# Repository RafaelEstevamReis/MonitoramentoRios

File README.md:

# MonitoramentoRios

Repositório do Projeto de Monitoramento de Rios

Acesse o sistema que monitora Rolante no Rio Grande do Sul: [Acessar](https://rios.bitcoineaqui.com.br/)

## Objetivo

Este repositório tem por objetivo desenvolver uma stack de Software e Hardware para monitoramento atmosférico, pluvial e fluvial, com o objetivo de publicar de forma aberta dados precisos a todos que precisarem.

## Arquitetura

O é Sistema altamente integrável, permitindo tanto o uso do Hardware desenvolvido aqui quanto integração de fontes externas, além de ser distribuído replicado em locais geograficamente afastados para redundância e proteção. 

Focando em baixo custo a Placa-mãe foi desenvolida pelo projeto para utilização de sensores amplamente disponíveis

### Detalhes do Hardware

Hardware baseado em ESP32 utilizando PCB customizada para o ambiente úmido da beira de rios mas compatível com DevKits como NodeMCU

Firmware baseado na Stack ESP-Home pela melhor curva de aprendizado de novos colaboradores

### Detalhes do Software

Backend redundante e integrado, recebe dados diretamente de estações, de servidor MQTT externo, de outros Backends, e integrações de sistemas externos

Frontend em Html/JS puro para leveza a simplicidade de treinamento e manutenção

## Agradecimentos Especiais

* A todas as doações em Bitcoin para o projeto [Bitcoin é Aqui](https://bitcoineaqui.com.br) que financiaram a pesquisa e desenvolvimento do projeto
* Ao [Geoge Silva](https://github.com/nitroxgas) por lançar a ideia e desenvolver o primeiro protótipo

## Posso usar o software ou hardware que este repositório desenvolve?

SIM!, mas com ressalvas.

O objetivo deste projeto é compartilhar informações, porém há muitas entidades que coletam os dados e os fecham, tornando-os inúteis para um amplo acesso.
Portanto, se você compartilha seus dados, você pode usar os nossos; se você restringe seus dados, você não pode usar os nossos.

Leia mais abaixo o texto completo do licenciamento antes de contribuir ou utilizar este repositório.

## Como replicar na minha cidade?

Você pode tanto replicar o sistema aqui desenvolvido por conta como integrar ao sistema já mantido pelo Projeto

Para integrar sua cidade no sistema já existente entre em contato com o [Bitcoin é Aqui](https://bitcoineaqui.com.br) ou com a [ACISA de Rolante](https://acisarolante.com/)

## Licença

Este repositório está licenciado sob uma dupla licença (`MIT` e `Licença Restrita`). Leia atenciosamente antes de contribuir e usar os dados gerados por estes softwares e hardwares.

A licença geral é MIT. No entanto, se você coleta, fornece e/ou processa dados de monitoramento atmosférico, manancial, fluvial, pluvial ou semelhantes, está sujeito às seguintes condições: Se os dados que você coleta são fechados, privados, compartilhados com limitações de acesso ou licenciamento, possuem mecanismos de controle de acesso, e/ou limitações na forma de acesso, então você não pode acessar, visualizar, compartilhar, utilizar, ou divulgar os dados coletados e gerados por este repositório e suas derivações. Nestes casos, você está sujeito à `Licença Restrita`.

Adicionalmente, se você é órgão governamental ou à serviço do serviço público, você precisa pedir autorização prévia para o uso dos dados.

### Licença Restrita

~~~
Termos de Uso da Licença Restrita

Esta licença estabelece os termos sob os quais os dados coletados e processados  podem ser acessados. Ao acessar ou utilizar estes dados, você concorda com os seguintes termos:

1. Proibição de Uso:

Os dados fornecidos por este repositório não podem ser utilizados para qualquer finalidade, seja ela comercial ou não comercial.

2. Proibição de Modificação:

Você não tem permissão para modificar, adaptar, ou criar obras derivadas dos dados fornecidos por este repositório.

3. Proibição de Redistribuição:

Você não pode redistribuir, compartilhar, publicar, ou de qualquer forma disponibilizar os dados a terceiros.

4. Proibição de Acesso Automatizado:

O acesso automatizado aos dados (por exemplo, via scripts, bots, ou outras ferramentas de automação) é estritamente proibido.

5. Proibição de Análise e Processamento:

Qualquer forma de análise ou processamento adicional dos dados coletados por este repositório é estritamente proibida.

6. Confidencialidade:

Você deve manter a confidencialidade dos dados acessados e não deve divulgar, publicar, ou de qualquer forma tornar públicos esses dados.

7. Penalidades

Qualquer violação dos termos desta licença pode resultar em medidas legais, incluindo, mas não se limitando a, ações civis e criminais.

8. Acordo

Ao acessar ou utilizar os dados fornecidos por este repositório, você reconhece que leu, entendeu e concorda em cumprir todos os termos desta licença. Se você não concorda com estes termos, não deve acessar ou utilizar os dados.
~~~

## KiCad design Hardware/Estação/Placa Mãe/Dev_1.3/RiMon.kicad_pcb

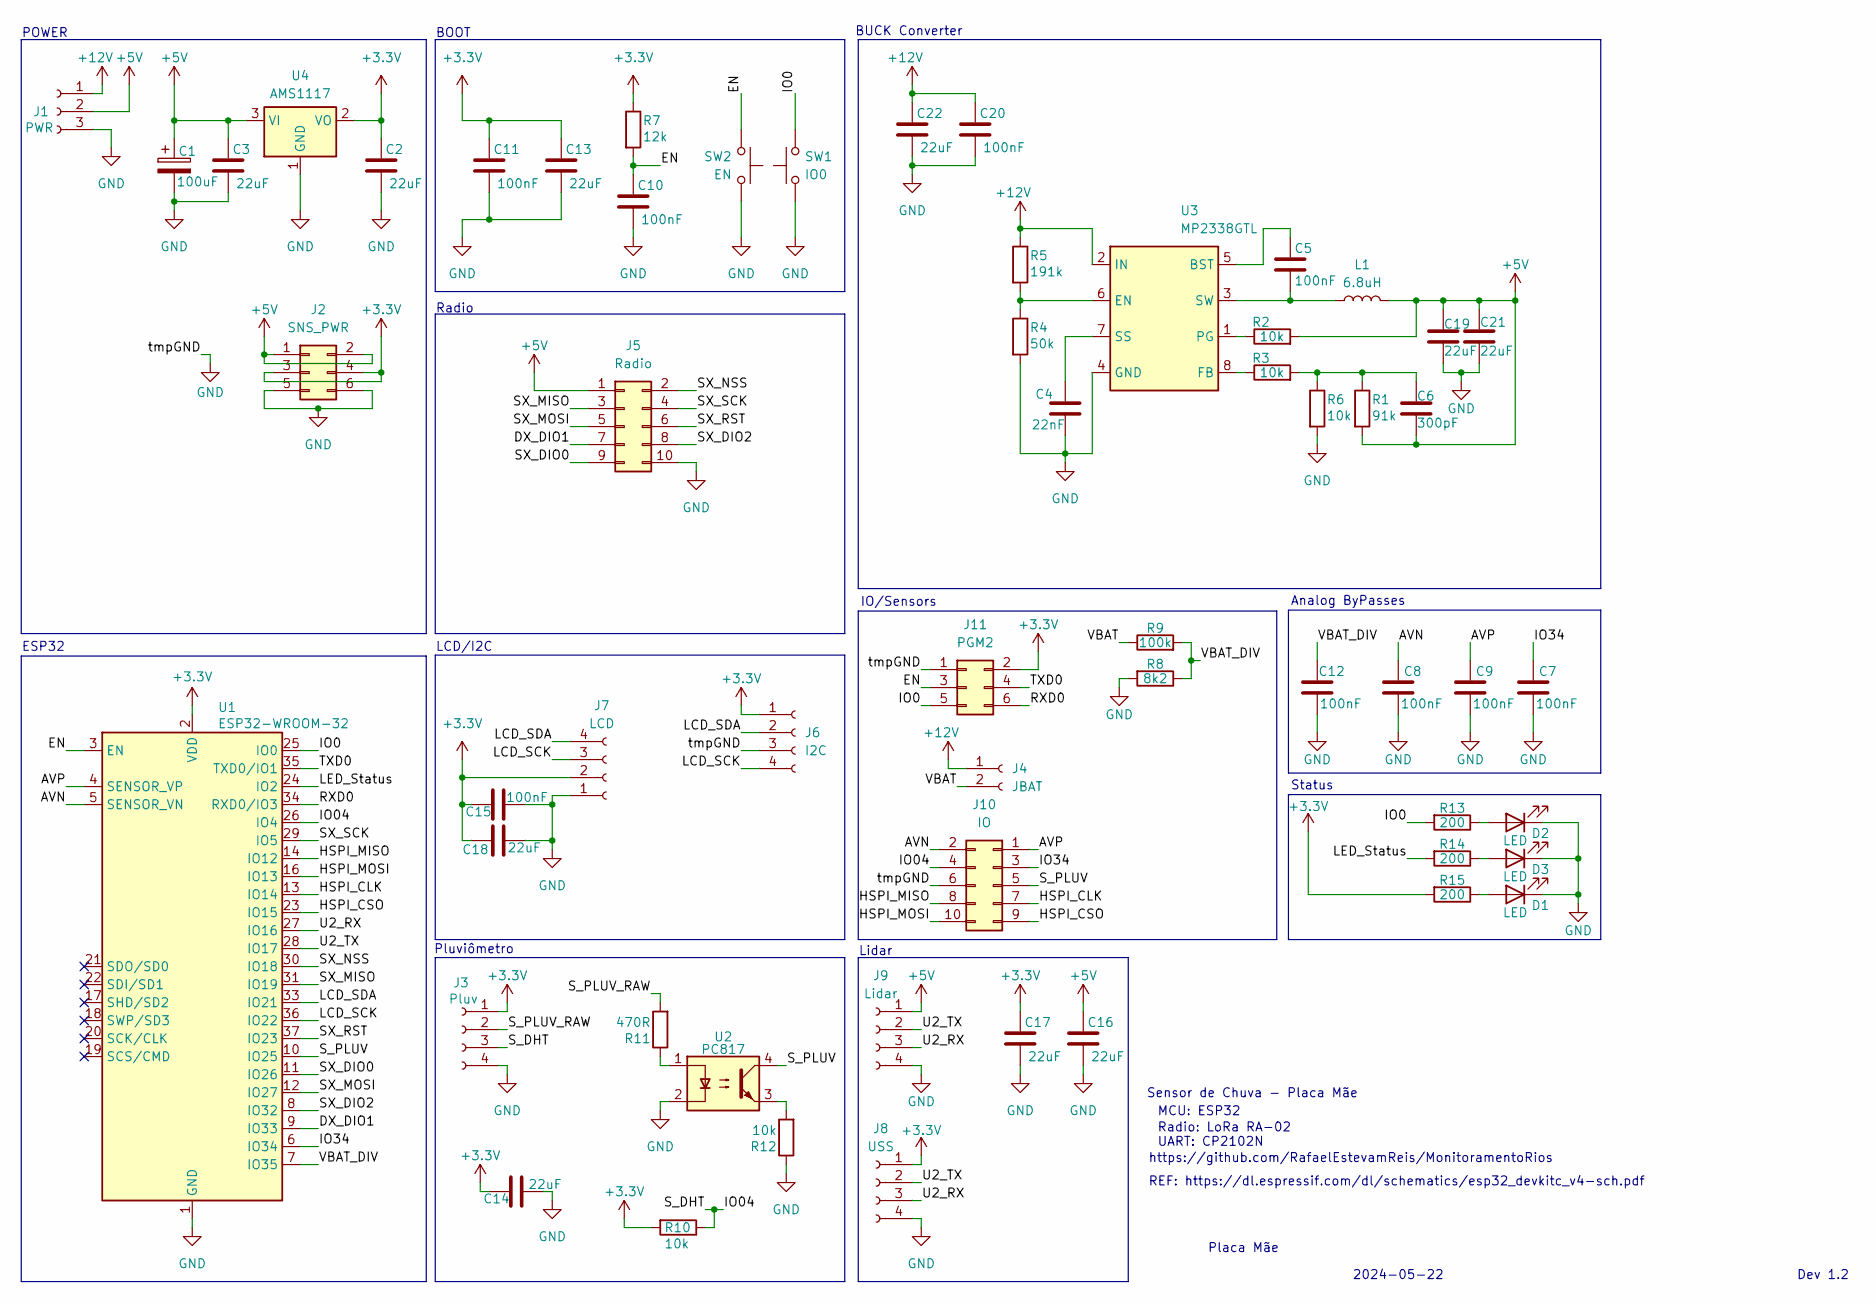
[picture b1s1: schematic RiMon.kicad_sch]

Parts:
C1: 100uF; CP_Elec_6.3x5.7
C2, C3, C14, C16, C17, C18: 22uF; C_0805_2012Metric_Pad1.18x1.45mm_HandSolder
C4: 22nF; C_0805_2012Metric_Pad1.18x1.45mm_HandSolder
C5, C7, C8, C9, C10, C11, C12, C15, C20: 100nF; C_0805_2012Metric_Pad1.18x1.45mm_HandSolder
C6: 300pF; C_0805_2012Metric_Pad1.18x1.45mm_HandSolder
C13, C19, C21, C22: 22uF; C_1206_3216Metric_Pad1.33x1.80mm_HandSolder
D1, D2, D3: LED; LED_D3.0mm
J1: PWR; TerminalBlock_Phoenix_MKDS-1,5-3-5.08_1x03_P5.08mm_Horizont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
J2: SNS_PWR; PinSocket_2x03_P2.54mm_Vertical
J3: Pluv; TerminalBlock_Phoenix_MKDS-1,5-4-5.08_1x04_P5.08mm_Horizont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
J4: JBAT; PinSocket_1x02_P2.54mm_Vertical
J5: Radio; PinSocket_2x05_P2.54mm_Vertical
J6: I2C; PinSocket_1x04_P2.54mm_Vertical
J7: LCD; PinSocket_1x04_P2.54mm_Vertical
J8: USS; PinSocket_1x04_P2.54mm_Vertical
J9: Lidar; JST_PH_B4B-PH-K_1x04_P2.00mm_Vertical
J10: IO; PinSocket_2x05_P2.54mm_Vertical
J11: PGM2; PinSocket_2x03_P2.54mm_Vertical
L1: 6.8uH; L_Wuerth_HCI-1040
R1: 91k; R_0805_2012Metric_Pad1.20x1.40mm_HandSolder
R2, R3, R6, R10, R12: 10k; R_0805_2012Metric_Pad1.20x1.40mm_HandSolder
R4: 50k; R_0805_2012Metric_Pad1.20x1.40mm_HandSolder
R5: 191k; R_0805_2012Metric_Pad1.20x1.40mm_HandSolder
R7: 12k; R_0805_2012Metric_Pad1.20x1.40mm_HandSolder
R8: 8k2; R_0805_2012Metric_Pad1.20x1.40mm_HandSolder
R9: 100k; R_0805_2012Metric_Pad1.20x1.40mm_HandSolder
R11: 470R; R_0805_2012Metric_Pad1.20x1.40mm_HandSolder
R13, R14, R15: 200; R_0805_2012Metric_Pad1.20x1.40mm_HandSolder
SW1: IO0; SW_Push_1P1T_NO_6x6mm_H9.5mm
SW2: EN; SW_Push_1P1T_NO_6x6mm_H9.5mm
U1: ESP32-WROOM-32
U2: PC817; SSO-4_6.7x5.1mm_P2.54mm_Clearance8mm
U3: MP2338GTL; SOT-583-8
U4: AMS1117; SOT-223-3_TabPin2

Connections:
+3.3V: C2.1, C11.1, C13.1, C14.2, C15.2, C17.1, C18.1, J2.3, J2.4, J3.1, J6.1, J7.2, J8.1, J11.2, R7.1, R10.2, R15.2, U1.2 (VDD), U4.2 (VO)
+5V: C1.1, C3.1, C6.2, C16.1, C19.1, C21.1, J1.2, J2.1, J2.2, J5.1, J9.1, L1.2, R1.2, R2.2, U4.3 (VI)
+12V: C20.1, C22.1, J1.1, J4.1, R5.1, U3.2 (IN)
/AVN: C8.2, J10.2, U1.5 (SENSOR_VN)
/AVP: C9.2, J10.1, U1.4 (SENSOR_VP)
/DX_DIO1: J5.7, U1.9 (IO33)
/EN: C10.1, J11.3, R7.2, SW2.2, U1.3 (EN)
/HSPI_CLK: J10.7, U1.13 (IO14)
/HSPI_CSO: J10.9, U1.23 (IO15)
/HSPI_MISO: J10.8, U1.14 (IO12)
/HSPI_MOSI: J10.10, U1.16 (IO13)
/IO0: J11.5, R13.2, SW1.2, U1.25 (IO0)
/IO04: J3.3, J10.4, R10.1, U1.26 (IO4)
/IO34: C7.2, J10.3, U1.6 (IO34)
/LCD_SCK: J6.4, J7.3, U1.36 (IO22)
/LCD_SDA: J6.2, J7.4, U1.33 (IO21)
/LED_Status: R14.2, U1.24 (IO2)
/RXD0: J11.6, U1.34 (RXD0/IO3)
/SX_DIO0: J5.9, U1.11 (IO26)
/SX_DIO2: J5.8, U1.8 (IO32)
/SX_MISO: J5.3, U1.31 (IO19)
/SX_MOSI: J5.5, U1.12 (IO27)
/SX_NSS: J5.2, U1.30 (IO18)
/SX_RST: J5.6, U1.37 (IO23)
/SX_SCK: J5.4, U1.29 (IO5)
/S_PLUV: J10.5, U1.10 (IO25), U2.4
/S_PLUV_RAW: J3.2, R11.2
/TXD0: J11.4, U1.35 (TXD0/IO1)
/U2_RX: J8.3, J9.3, U1.27 (IO16)
/U2_TX: J8.2, J9.2, U1.28 (IO17)
/VBAT: J4.2, R9.1
/VBAT_DIV: C12.2, R8.1, R9.2, U1.7 (IO35)
GND: C1.2, C2.2, C3.2, C4.2, C7.1, C8.1, C9.1, C10.2, C11.2, C12.1, C13.2, C14.1, C15.1, C16.2, C17.2, C18.2, C19.2, C20.2, C21.2, C22.2, D1.1 (K), D2.1 (K), D3.1 (K), J1.3, J2.5, J2.6, J3.4, J5.10, J6.3, J7.1, J8.4, J9.4, J10.6, J11.1, R4.2, R6.2, R8.2, R12.1, SW1.1, SW2.1, U1.1 (GND), U1.15 (GND), U1.38 (GND), U1.39 (GND), U2.2, U3.4 (GND), U4.1 (GND)
unnamed: C6.1, R1.1, R3.2, R6.1
unnamed: D1.2 (A), R15.1
unnamed: D2.2 (A), R13.1
unnamed: D3.2 (A), R14.1
unnamed: R11.1, U2.1
unnamed: R12.2, U2.3
unnamed: C5.1, U3.5 (BST)
unnamed: R4.1, R5.2, U3.6 (EN)
unnamed: R3.1, U3.8 (FB)
unnamed: R2.1, U3.1 (PG)
unnamed: C4.1, U3.7 (SS)
unnamed: C5.2, L1.1, U3.3 (SW)

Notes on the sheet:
IO/Sensors
BOOT
Pluviômetro
Lidar
Status
Placa Mãe
https://github.com/RafaelEstevamReis/MonitoramentoRios
2024-05-22
LCD/I2C
Dev 1.2
Radio: LoRa RA-02
Analog ByPasses
UART: CP2102N
Radio
MCU: ESP32
BUCK Converter
Sensor de Chuva - Placa Mãe
POWER
ESP32
REF: https://dl.espressif.com/dl/schematics/esp32_devkitc_v4-sch.pdf

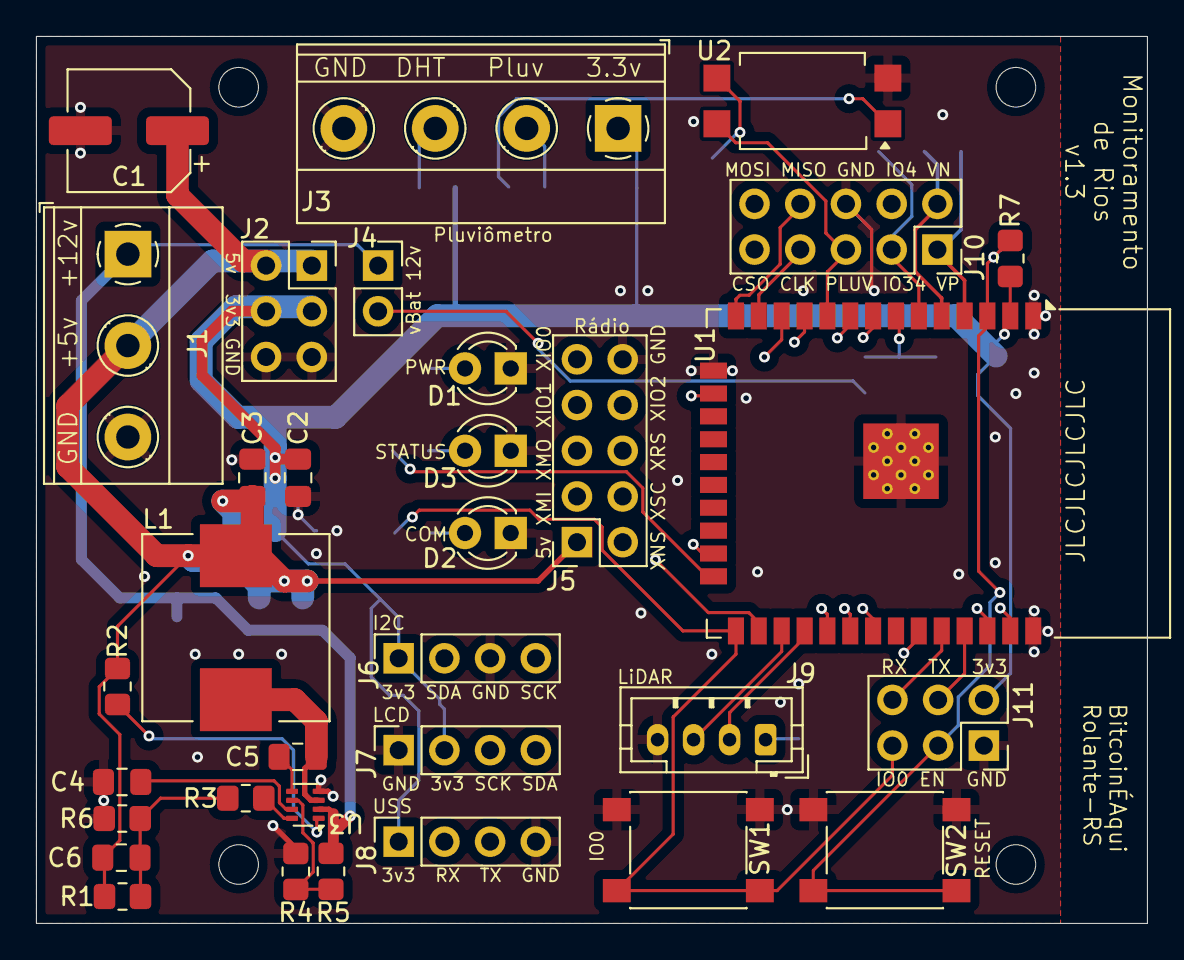
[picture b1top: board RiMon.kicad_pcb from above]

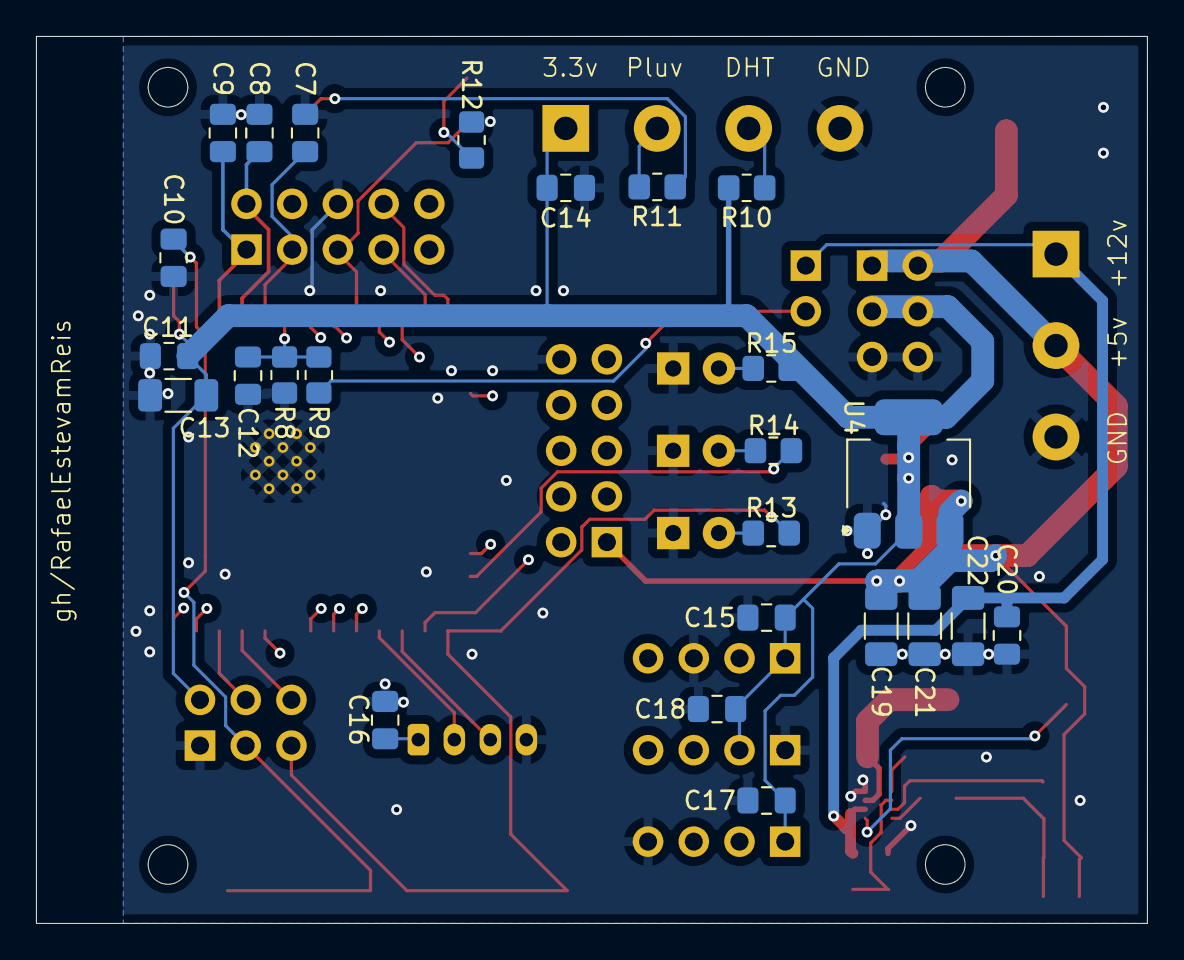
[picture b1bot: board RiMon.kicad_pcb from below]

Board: 4 copper layers, 61.7 x 49.3 mm, 58 parts (25 on the bottom side), 45 nets.

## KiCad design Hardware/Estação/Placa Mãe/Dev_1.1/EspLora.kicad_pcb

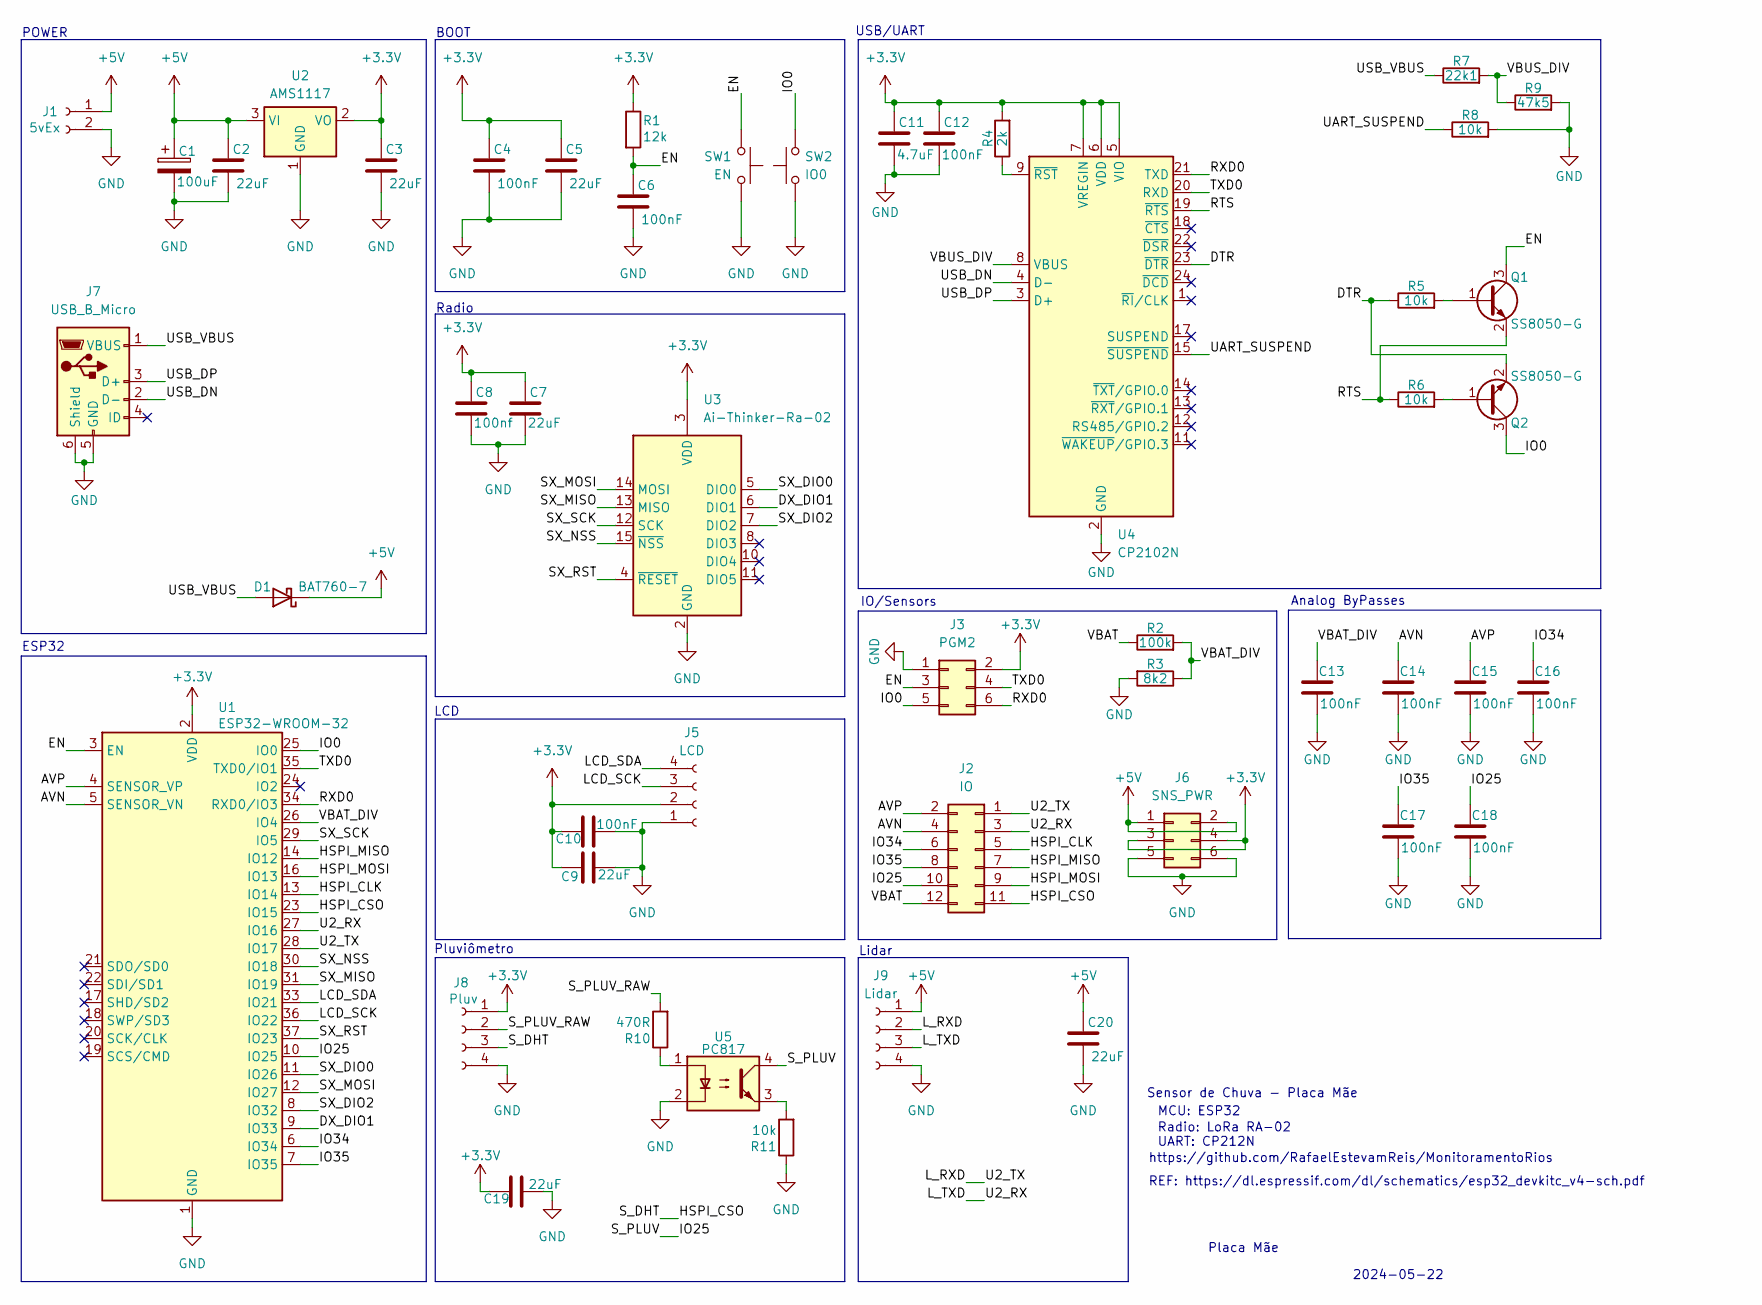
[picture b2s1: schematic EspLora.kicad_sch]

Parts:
C1: 100uF; CP_Elec_6.3x5.7
C2, C3, C5, C7, C9, C20: 22uF; C_1206_3216Metric_Pad1.33x1.80mm_HandSolder
C4, C6, C10, C12, C13, C14, C15, C16, C17, C18: 100nF; C_0805_2012Metric_Pad1.18x1.45mm_HandSolder
C8: 100nf; C_0805_2012Metric_Pad1.18x1.45mm_HandSolder
C11: 4.7uF; C_1206_3216Metric_Pad1.33x1.80mm_HandSolder
C19: 22uF; C_0805_2012Metric_Pad1.18x1.45mm_HandSolder
D1: BAT760-7; D_SOD-323_HandSoldering
J1: 5vEx; TerminalBlock_Phoenix_MKDS-1,5-2-5.08_1x02_P5.08mm_Horizont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
J2: IO; PinSocket_2x06_P2.54mm_Vertical
J3: PGM2; PinSocket_2x03_P2.54mm_Vertical
J5: LCD; PinSocket_1x04_P2.54mm_Vertical
J6: SNS_PWR; PinSocket_2x03_P2.54mm_Vertical
J7: USB_B_Micro; USB_Micro-B_GCT_USB3076-30-A
J8: Pluv; TerminalBlock_Phoenix_MKDS-1,5-4-5.08_1x04_P5.08mm_Horizont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
J9: Lidar; JST_PH_B4B-PH-K_1x04_P2.00mm_Vertical
Q1, Q2: SS8050-G; SOT-23
R1: 12k; R_0805_2012Metric_Pad1.20x1.40mm_HandSolder
R2: 100k; R_0805_2012Metric_Pad1.20x1.40mm_HandSolder
R3: 8k2; R_0805_2012Metric_Pad1.20x1.40mm_HandSolder
R4: 2k; R_0805_2012Metric_Pad1.20x1.40mm_HandSolder
R5, R6, R8, R11: 10k; R_0805_2012Metric_Pad1.20x1.40mm_HandSolder
R7: 22k1; R_0805_2012Metric_Pad1.20x1.40mm_HandSolder
R9: 47k5; R_0805_2012Metric_Pad1.20x1.40mm_HandSolder
R10: 470R; R_0805_2012Metric_Pad1.20x1.40mm_HandSolder
SW1: EN; SW_Push_1P1T_NO_CK_KMR2
SW2: IO0; SW_Push_1P1T_NO_CK_KMR2
U1: ESP32-WROOM-32
U2: AMS1117; SOT-223-3_TabPin2
U3: Ai-Thinker-Ra-02; Ai-Thinker-Ra-01-LoRa
U4: CP2102N; QFN-24-1EP_4x4mm_P0.5mm_EP2.6x2.6mm
U5: PC817; SOP-4_3.8x4.1mm_P2.54mm

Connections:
+3.3V: C3.1, C4.1, C5.1, C7.1, C8.1, C9.1, C10.2, C11.1, C12.1, C19.2, J3.2, J5.2, J6.3, J6.4, J8.1, R1.1, R4.2, U1.2 (VDD), U2.2 (VO), U3.3 (VDD), U4.5 (VIO), U4.6 (VDD), U4.7 (VREGIN)
+5V: C1.1, C2.1, C20.1, D1.1 (K), J1.1, J6.1, J6.2, J9.1, U2.3 (VI)
/AVN: C14.2, J2.4, U1.5 (SENSOR_VN)
/AVP: C15.2, J2.2, U1.4 (SENSOR_VP)
/DTR: Q2.2 (E), R5.1, U4.23 (~DTR)
/DX_DIO1: U1.9 (IO33), U3.6 (DIO1)
/EN: C6.1, J3.3, Q1.3 (C), R1.2, SW1.2, U1.3 (EN)
/HSPI_CLK: J2.5, U1.13 (IO14)
/HSPI_CSO: J2.11, J8.3, U1.23 (IO15)
/HSPI_MISO: J2.7, U1.14 (IO12)
/HSPI_MOSI: J2.9, U1.16 (IO13)
/IO0: J3.5, Q2.3 (C), SW2.2, U1.25 (IO0)
/IO25: C18.2, J2.10, U1.10 (IO25), U5.4
/IO34: C16.2, J2.6, U1.6 (IO34)
/IO35: C17.2, J2.8, U1.7 (IO35)
/LCD_SCK: J5.3, U1.36 (IO22)
/LCD_SDA: J5.4, U1.33 (IO21)
/L_RXD: J2.1, J9.2, U1.28 (IO17)
/L_TXD: J2.3, J9.3, U1.27 (IO16)
/RTS: Q1.2 (E), R6.1, U4.19 (~RTS)
/RXD0: J3.6, U1.34 (RXD0/IO3), U4.21 (TXD)
/SX_DIO0: U1.11 (IO26), U3.5 (DIO0)
/SX_DIO2: U1.8 (IO32), U3.7 (DIO2)
/SX_MISO: U1.31 (IO19), U3.13 (MISO)
/SX_MOSI: U1.12 (IO27), U3.14 (MOSI)
/SX_NSS: U1.30 (IO18), U3.15 (~NSS)
/SX_RST: U1.37 (IO23), U3.4 (~RESET)
/SX_SCK: U1.29 (IO5), U3.12 (SCK)
/S_PLUV_RAW: J8.2, R10.2
/TXD0: J3.4, U1.35 (TXD0/IO1), U4.20 (RXD)
/UART_SUSPEND: R8.1, U4.15 (~SUSPEND)
/USB_DN: J7.2 (D-), U4.4 (D-)
/USB_DP: J7.3 (D+), U4.3 (D+)
/USB_VBUS: D1.2 (A), J7.1 (VBUS), R7.1
/VBAT: J2.12, R2.1
/VBAT_DIV: C13.2, R2.2, R3.1, U1.26 (IO4)
/VBUS_DIV: R7.2, R9.1, U4.8 (VBUS)
GND: C1.2, C2.2, C3.2, C4.2, C5.2, C6.2, C7.2, C8.2, C9.2, C10.1, C11.2, C12.2, C13.1, C14.1, C15.1, C16.1, C17.1, C18.1, C19.1, C20.2, J1.2, J3.1, J5.1, J6.5, J6.6, J7.5 (GND), J7.6 (Shield), J8.4, J9.4, R3.2, R8.2, R9.2, R11.1, SW1.1, SW2.1, U1.1 (GND), U1.15 (GND), U1.38 (GND), U1.39 (GND), U2.1 (GND), U3.1 (GND), U3.2 (GND), U3.9 (GND), U3.16 (GND), U4.2 (GND), U4.25 (GND), U5.2
unnamed: Q1.1 (B), R5.2
unnamed: Q2.1 (B), R6.2
unnamed: R10.1, U5.1
unnamed: R11.2, U5.3
unnamed: R4.1, U4.9 (~RST)

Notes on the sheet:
IO/Sensors
BOOT
Pluviômetro
Lidar
Placa Mãe
https://github.com/RafaelEstevamReis/MonitoramentoRios
2024-05-22
LCD
Radio: LoRa RA-02
Analog ByPasses
UART: CP212N
Radio
MCU: ESP32
USB/UART
Sensor de Chuva - Placa Mãe
POWER
ESP32
REF: https://dl.espressif.com/dl/schematics/esp32_devkitc_v4-sch.pdf

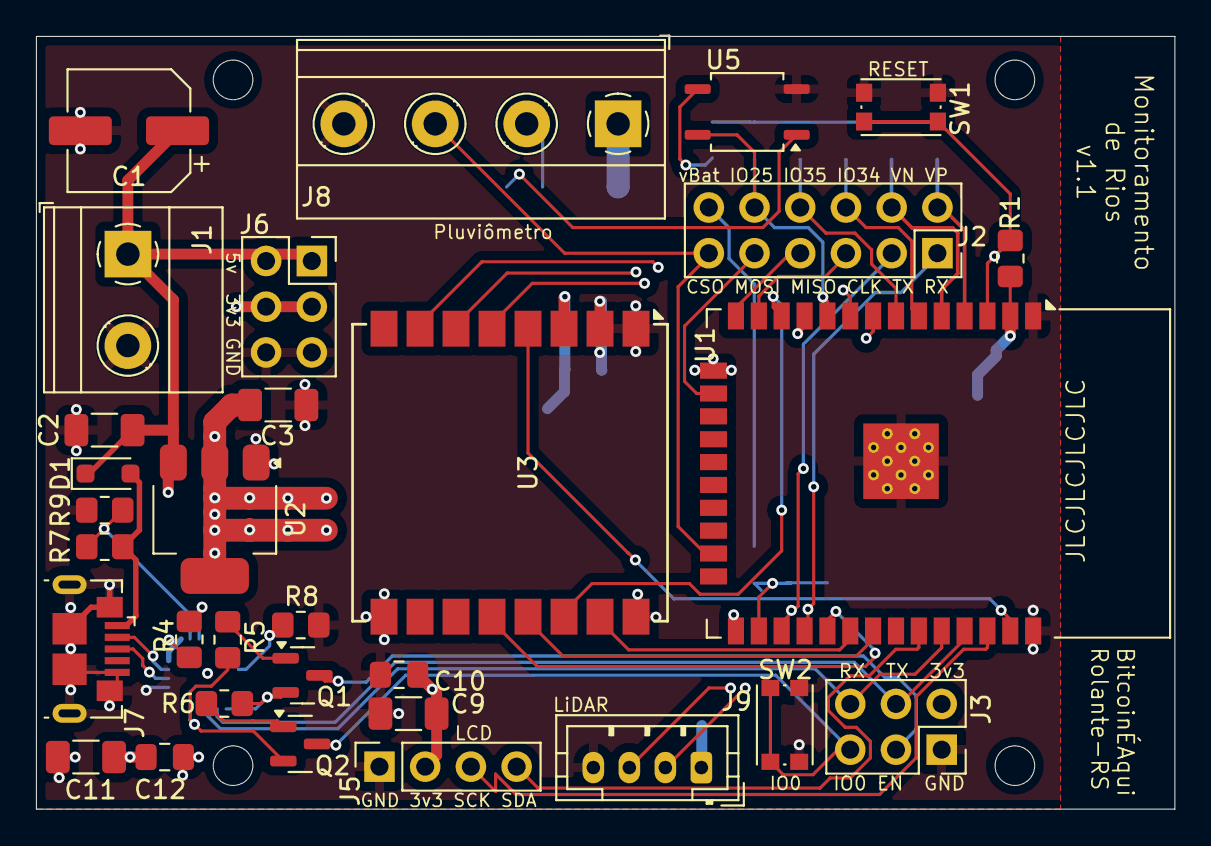
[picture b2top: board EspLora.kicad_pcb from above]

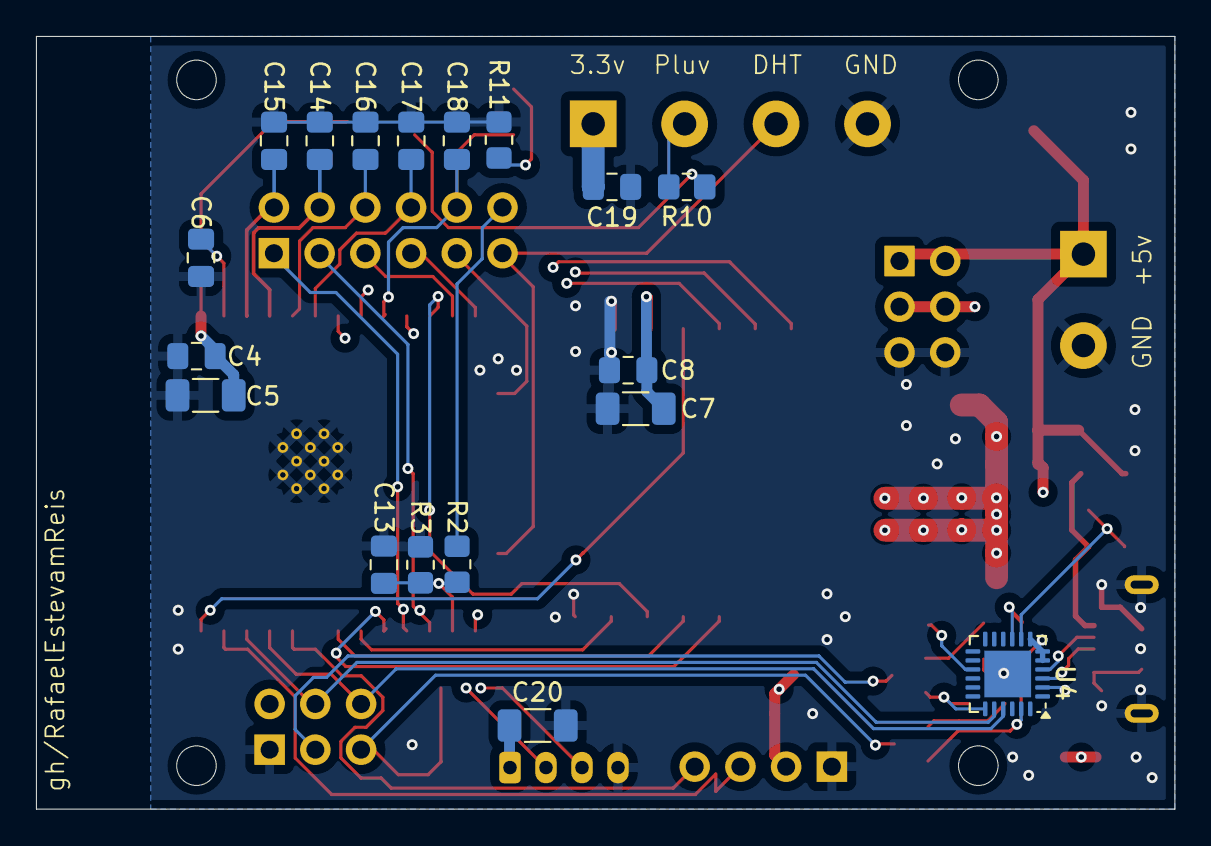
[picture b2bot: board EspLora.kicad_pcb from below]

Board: 4 copper layers, 63.2 x 42.9 mm, 49 parts (18 on the bottom side), 43 nets.

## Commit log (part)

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2024-09-25 Sensores de primeira geração não tem pressão
2024-11-20 Progresso alterações
2024-11-20 Finaliza traces v1.2
2024-11-25 Hardware v1.3
2024-11-25 Ajustes visuais nível em gráfico
2024-11-26 v1.3 conectado e organizado
2024-11-26 Limpeza geral
2024-11-27 Adiciona busca por Nome
2024-11-27 Trata casing e null
2024-11-27 Adiciona robots.txt
2024-11-28 Finaliza Design
2024-11-28 Ajustes fabricação
2024-11-28 Produção
2024-12-01 Adiciona cor
2024-12-01 Fixa cores para estações conhecidas
2024-12-02 Adiciona percentual da bateria no site
2024-12-02 Ajusta tabela
2024-12-02 Corrige BD Data
2024-12-02 Adiciona formatação de valor
2024-12-02 Move nome da estação e adiciona idade do dado
2024-12-02 Refatoração das tabelas
2024-12-03 Página Live
2024-12-03 Corrige ctrl
2024-12-06 Publica link /live
2024-12-06 Corrige gráfico de nível do Rio
2024-12-07 Agregador de valores
2024-12-07 Adiciona Round que suporta null
2024-12-08 Adiciona filtros
2024-12-08 Adiciona agregador de dados
2024-12-08 Adiciona dados por hora
2024-12-08 Finaliza agregador
2024-12-08 Atualiza função e Remove dados Hora
2024-12-08 Remove linha DELETE
2024-12-08 Adiciona gráfico
2024-12-08 Ajusta UTC
2024-12-08 Trás script de gráfico para dentro
2024-12-08 Adiciona mapa
2024-12-08 Adiciona CORS
2024-12-08 Oculta métodos POST
2024-12-10 Remove NonAction
2024-12-10 Retorna NULL ao invés de zero
2024-12-12 Tela comparativa
2024-12-14 Adiciona proteção contra dados inválidos
2024-12-14 Teste upload imagem
2024-12-14 Upload de imagem
2024-12-14 Ajusta para UTC
2024-12-14 Faz mapa exibir estações desconectadas
2024-12-14 Nova fórmula de último
2024-12-14 Adiciona NoSig e refatora laço
2024-12-14 Refaz Agregador
2024-12-14 Desativa DELETE
2024-12-14 Ajuste de horário no Live
2024-12-14 Nova Home
2024-12-14 Adiciona nível alerta
2024-12-15 Altera filtro de null
2024-12-15 Corrige contagem
2024-12-17 Adiciona UltimoEnvio
2024-12-17 Adiciona listagem de estações
2024-12-17 Adiciona Nome da Estaçõ
2024-12-18 Adiciona url gh
2025-01-02 Testes firmware não-ESPHome
2025-01-06 Adiciona suporte
2025-01-30 Ativa Novas Estações
2025-01-30 Adiciona RSRZ-CH01
2025-02-10 Adiciona Debug
2025-02-10 Suporte EspCam
2025-02-10 Suporte 18650
2025-02-10 Usável em Mobile
2025-02-10 Esconder gráfico se não tiver dados
2025-02-10 Refatora links
2025-02-10 Adiciona página de manutenção
2025-02-11 Ajusta decimais
2025-02-11 Mais casas decimais
2025-02-24 Habilita estações
2025-02-24 Adiciona CE01
2025-02-24 Adiciona Gráfico do Chuvisqueiro
2025-02-24 Ajuste de CSS
2025-02-24 Atualizações modelos
2025-03-26 Remove páginas antigas
2025-03-26 Adiciona FavIcon do BitcoinEAqui
2025-03-26 Manutenção abre estação em nova janela
2025-03-26 Tabelas aguardam com "Carregando"
2025-03-26 Ajuste de horário e gráficos
2025-03-26 Permite clicar no gráfico da estação para detalhar
2025-03-26 Grava Nonce
2025-03-27 Implementa Archiver
2025-03-27 Corrige tempo
2025-04-11 Adiciona SuporteLoRa
2025-04-11 Ativa Vacuum
2025-04-11 Permite selecionar intervalo dos dados
2025-04-11 Não responde campos null
2025-04-11 Comprime resposta
2025-04-11 Adiciona Cache para lastHourly
2025-04-11 Desativa RawData no últimos
2025-04-15 Corrige tela de manutenção
2025-04-16 Helper ToDecimal
2025-04-16 Adiciona Type no retorno
2025-04-16 Adiciona MQTT
2025-04-16 Exibe origem LoRa da linha
2025-04-16 Log de dados
2025-04-16 Adiciona DataHoraDadosUTC
2025-04-18 Migra identificação para Source
2025-04-18 Aumenta limite da tela de detalhes
2025-04-19 Remove filtro aonde precisa ter negativo
2025-04-24 Adiciona campo precipitação
2025-04-24 Formata dados Chuva
2025-04-24 Adiciona Precipitação 10min
2025-04-25 Envia precipitação 10min
2025-04-25 Melhora exibição precipitação
2025-04-25 Arruma tabs
2025-04-25 Altera resposta para "10min"
2025-04-25 Ajuste dos pontos para melhor visibilidade
2025-04-25 Ajuste área de click
2025-04-25 Ajustes visuais home
2025-04-25 Gráfico de chuva
2025-04-25 Reduz espaçamento das letras
2025-04-28 Adiciona Precipitação Total
2025-04-28 Corrige exibição de zeros
2025-04-28 Suporte à reset
2025-04-28 Converte gráfico para mm/h
2025-04-29 Gráfico de barras
2025-04-29 Arruma negativos
2025-04-29 Corrige agregador de NULL
2025-04-29 Corrige exibição
2025-04-29 Corrige NAN
2025-04-29 Gráfico de barras apenas para chuva
2025-05-01 Create LoraTx
2025-05-12 Refatora agregado
2025-05-12 Implementa DataPurge
2025-05-19 Corrige Maintenance
2025-05-19 Corrige "última hora"
2025-05-19 Adiciona ribbon BETA
2025-05-19 Corrige clipboard
2025-05-20 Typo
2025-05-20 Corrige agregador
2025-05-22 getCurrentHourKey
2025-05-24 Adiciona Acumulador
2025-05-26 Adiciona suporte à reset
2025-06-06 Atualiza /live para horário local
2025-06-17 Migra nova para maint
2025-06-17 Inverte ordem gráficos home
2025-06-17 Adiciona mm/h na home
2025-06-18 Remove Cache do lastHourly
2025-06-18 Arruma NAN e textos
2025-06-18 Refaz Home com nível e acumulado
2025-06-18 Adiciona Nível Normal
2025-06-18 Ajutes de texto
2025-06-18 Adiciona gráfico de chuva no detalhamento
2025-06-18 Adiciona Logging de acesso
2025-06-18 Adiciona response Len
2025-06-18 Corrige parametro nomeado
2025-06-18 Corrige acumulador móvel
2025-06-18 Adiciona unidades
2025-06-19 Proteção contra string vazia
2025-06-19 Filtra estações EX
2025-06-19 Bump Simple.Api
2025-06-19 Bump Simple.Sqlite
2025-06-19 Bump Serilog
2025-06-19 Bump Swashbuckle.AspNetCore
2025-06-19 Deixa gravação estática
2025-06-19 Adiciona tabela TBCatalogarExternas
2025-06-19 Adiciona ExternalArchiver
2025-06-19 Atualiza Archiver para nome
2025-06-19 Melhorias no Archiver
2025-06-19 Adiciona Ac12h
2025-06-20 Corrige Cores
2025-06-20 Oculta alerta se nível baixo
2025-06-21 Corrige offset de datas
2025-06-21 Refatora home para celular
2025-06-21 Refatoração CSS
2025-06-22 Adiciona encaixe parafuso
2025-06-22 Troca OnClick para a-href
2025-06-23 Melhorias visuais
2025-06-23 Muda estilo da legenda
2025-06-23 Coleta vento e insolação
2025-06-23 Oculta ícone da bateria se sem dados
2025-06-27 Ajuste nível NORMAL da RSRL-GLLS
2025-06-27 Texto Sobre
2025-06-27 Update README.md
    Correção de Typos
2025-06-28 Implementa calibração digital
2025-06-28 Adiciona espera
2025-06-29 Implementa Weather via MeteoBlue
2025-06-29 Ativa MeteoBlue Worker
2025-06-29 Ajusta tempo e coordenada
2025-06-29 Corrige temRecente
2025-06-29 Extrai imagem da coinos para fora da Home
2025-06-29 Migra para SVG
2025-06-29 Adiciona AgregadoHoraRange
2025-06-29 Salvar agregado para vazio
2025-06-29 Limpeza
2025-06-29 Adiciona ToolTip
2025-06-30 Arquivos 3D
2025-06-30 Controller Weather
2025-06-30 Adiciona Weather na HomePage
2025-06-30 Adiciona data/hora dos dados de previsão
2025-06-30 Corrige horário ObterWeatherProximasHoras()
2025-06-30 Corrige ambiguidade
2025-06-30 Ajusta ícone chuva com base na medida
2025-06-30 Refeito UI da previsão
2025-06-30 Ediciona edição de Estação
2025-06-30 Adiciona CEMADEN
2025-06-30 Remove Debug
2025-06-30 Refatora exibição de listagem
2025-07-01 Muda exibição de vento
2025-07-01 Apenas se >10%
2025-07-01 Implementa WL-SKIP
2025-07-02 Altera intervalo da previsão para <2/d
2025-07-02 Altera sequenciamento de leitura das estações externas
2025-07-02 Altera casas decimais para T<10
2025-07-02 Grava id isnerido
2025-07-02 Corrige NaN por duplo Z
2025-07-02 Capturar GitCommit
2025-07-02 Gerar gitHash no build
2025-07-02 Disponibiliza versão no controller
2025-07-02 Corrige índice
2025-07-02 Testa duas opções de geração em Build
2025-07-02 Mantém versão TEMPLATE
2025-07-02 Migra /home.html para Index
2025-07-02 Update Dockerfile
2025-07-02 Implementa edição de estação com reset de Key
2025-07-02 Corrige APIKEY override
2025-07-03 Ajustes texto Home
2025-07-04 Se tem apenas Temp2, utiliza como primária
2025-07-04 Adiciona pressão nos detalhes e refatora
2025-07-04 Troca externas de 4/h para 5/h
2025-07-04 Gráfico bateria
2025-07-04 Ajusta margens Index
2025-07-04 Adiciona gráfico de pressão no detalhamento
2025-07-05 Desativa RLRS-GLLS/CD20250627_vBat
2025-07-05 Melhora gráficos /estacao
2025-07-05 Corrige Urls
2025-07-05 Adiciona mapa completo
2025-07-05 Mapa com bolha Multi-Dados
2025-07-06 Preenche EX.Precipitacao10m
2025-07-06 Adiciona Query no [REQ] Log
2025-07-06 Corrige gráfico de bateria
2025-07-06 Adiciona gráficos
2025-07-06 Melhorias UI
2025-07-06 Ativa estação RSRL-AR01 na home
2025-07-07 Ajustes visuais
2025-07-08 Troca níveis bateria
2025-07-10 Explicita cabeçado do gráfico
2025-07-15 Adiciona endpoint para weather extendido
2025-07-15 Adiciona previsão extendida
2025-07-15 Refatora Index
2025-07-15 Ajusta centro do mapa em celular
2025-07-16 Correções de conversão UTC
2025-07-16 Correção de Id
2025-07-16 Forçar geração de dados Hourly
2025-07-16 Adiciona PictoCode
2025-07-16 Imagens PictoCode
2025-07-17 Corrige reset no acumulador
2025-07-17 Reduz startup do MeteoBlue
2025-07-17 Corrige gráfico de precipitação
2025-07-25 Logar calibrações carregadas
2025-07-25 Adiciona calibração para ignorar a raíz
2025-07-27 Muda previsão estendida para vários dias
2025-07-27 Retorna BE01 para Index
2025-07-27 Adiciona Página /tempo
2025-07-27 Remove /ext
2025-07-27 CSS funciona
2025-07-27 MeteoBlue com tempo reduzido se tem chuva
2025-07-27 Desativa probabilidade de chuva na home
2025-07-27 Adiciona na tela coordenada da previsão
2025-07-27 Remove legenda inferior dos gráficos
2025-07-27 Melhora visibilidade
2025-07-28 Corrige valor de debug
2025-08-03 Usa META Refresh na index
2025-08-03 Ajusta faixa do gráfico para incluir a hora atual
2025-08-03 Inclui hora atual do BD
2025-08-03 Refatora estilos previsão
2025-08-04 Remove ferramenta de ocultar alerta
2025-08-04 Melhora descrição dos gráficos
2025-08-04 Implementa ordenação manual
2025-08-04 Atualiza revisão do index para r=5
2025-08-04 Adiciona RSRL-BV01 no mapa
2025-08-11 Adiciona NonceCheck para UpController
2025-08-14 Desativa calibração raíz
2025-08-14 Ajusta nova altura
2025-08-14 Desativa MQTT se não tiver HOST
2025-08-14 Não fazer Deploy do AppSettings
2025-08-14 Adicionar detalhes de versão
2025-08-14 Remove extensão
2025-08-14 Não executar STATIC na Azure
2025-08-14 Corrige Nonce
2025-08-14 Adiciona tipo SYNC
2025-08-14 Adiciona base de sincronia entre servidores
2025-08-16 Refatora Log Sync
2025-08-18 Renomeia componentes INDEX para RSRL
2025-08-18 Migra INDEX para roteador
2025-08-18 Corrige CD20250814_WL
2025-08-19 RSRL-CH01\CD20250819_WL
2025-08-19 Não carrega calibrações vencidas
2025-08-19 Melhora filtro [chart]Estação.temBat?
2025-08-19 Melhora exibição de estações sincronizadas
2025-08-19 Implementa código de região
2025-08-19 Refatora log região
2025-08-22 Troca CE01 do mapa para CE02
2025-08-28 Trata EXT-CDM com dados indisponíveis
2025-09-10 Atualiza calibração
2025-09-20 Ajusta calibração braço de medição
2025-10-15 Atualiza readme
2025-12-08 Remove comentário incorreto
2025-12-09 Aviso de manutenção
2025-12-10 Corrige ordenação da página resumo da estação
2025-12-10 Ajusta namespace
2025-12-29 Renomeia lista
2025-12-29 Nova RsRl 2
2025-12-29 Alteração nos Textos e exibição
2025-12-29 Agrupa previsão do tempo
2025-12-29 Migra Home
2025-12-29 Nova home RSRL
2025-12-29 Ajustes para telas pequenas
2025-12-29 Adiciona aviso de manutenção
2026-01-04 Remove "Ver Estação" da tabela
2026-01-10 Remove unused precipitation probability tag
2026-01-18 Adiciona gráfico de chuva no Morro Grande
2026-01-18 Adiciona ID da MG01 na lista de Chuva
2026-01-18 Refatora avisos de compilador
2026-03-30 Corrige bug em transações que não são divisíveis por 4
2026-03-31 Corrige busca de estação vazia
